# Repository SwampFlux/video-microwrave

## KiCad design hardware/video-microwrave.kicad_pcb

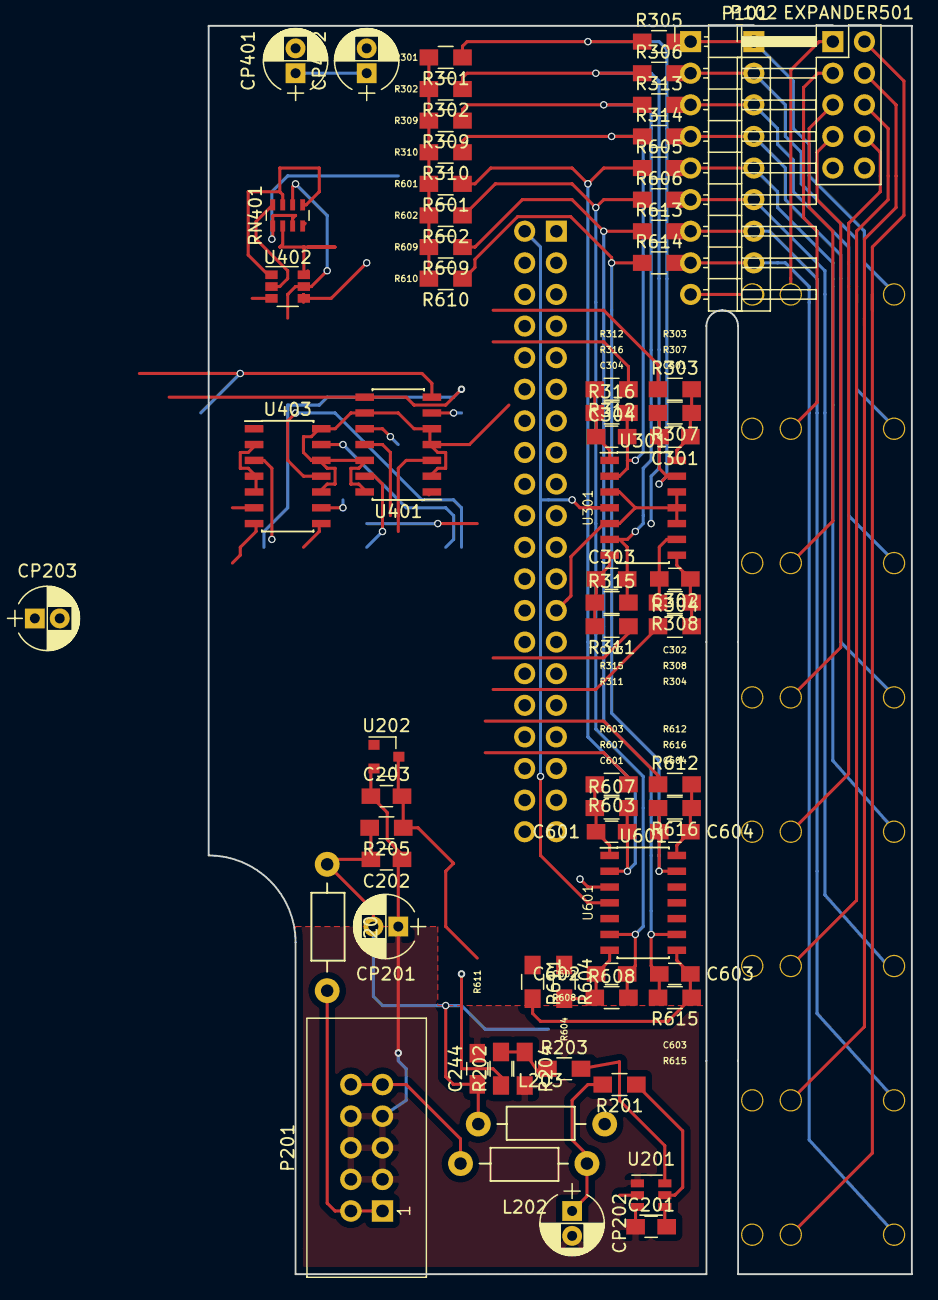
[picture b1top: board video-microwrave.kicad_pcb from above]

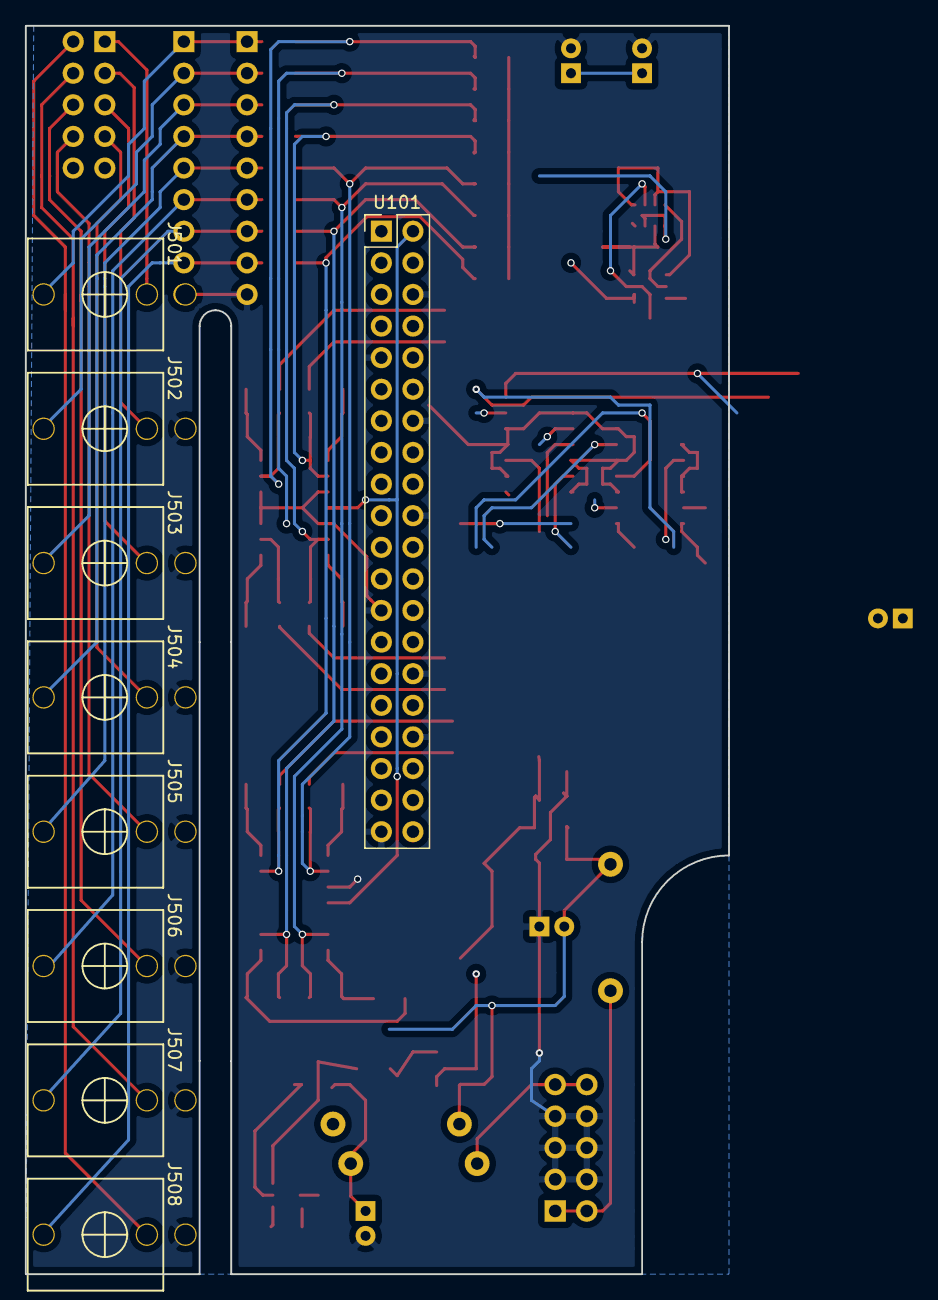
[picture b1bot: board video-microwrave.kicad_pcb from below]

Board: 2 copper layers, 56.5 x 100.3 mm, 78 parts (9 on the bottom side), 52 nets.

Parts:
C201, C244: 100nF; C_0805_HandSoldering
C202, C203: 1uF; C_0805_HandSoldering
C301, C302, C303, C304, C601, C602, C603, C604: 560pF; C_0805_HandSoldering
CP201, CP202, CP203: 22uF; CP_Radial_D5.0mm_P2.00mm
CP401: 100nF; CP_Radial_D5.0mm_P2.00mm
CP402: 10uF; CP_Radial_D5.0mm_P2.00mm
EXPANDER501: CONN_02X05; Pin_Header_Straight_2x05_Pitch2.54mm
J501, J502, J503, J504, J505, J506, J507, J508: PJ301M-12
L201, L202: 100nH; Choke_Horizontal_RM10mm
L203: 6u8H; Choke_Horizontal_RM10mm
P101: CONN_01X09; Pin_Header_Angled_1x09_Pitch2.54mm
P102: CONN_01X09; Pin_Header_Straight_1x09_Pitch2.54mm
P201: CONN_02X08; IDC_Header_Straight_10pins
R201: 100k; R_0805_HandSoldering
R202: 402k2; R_0805_HandSoldering
R203: 75k; R_0805_HandSoldering
R204: 7k68; R_0805_HandSoldering
R205: 2k; R_0805_HandSoldering
R301, R302, R309, R310, R601, R602, R609, R610: 499; R_0805_HandSoldering
R303, R304, R311, R312, R603, R604, R611, R612: 100R; R_0805_HandSoldering
R305, R306, R313, R314, R605, R606, R613, R614: 1k; R_0805_HandSoldering
R307, R308, R315, R316, R607, R608, R615, R616: 270; R_0805_HandSoldering
RN401: 10k; R_Array_Concave_4x0603
U101: Raspberry_Pi_Zero; Pin_Header_Straight_2x20_Pitch2.54mm
U201: LM1117-3.3; SOT-23-6
U202: NCP1117DT50G; SOT-23
U301, U601: MCP6004; SOIC-14_3.9x8.7mm_Pitch1.27mm
U401, U403: MCP3424; SOIC-14_3.9x8.7mm_Pitch1.27mm
U402: FDC6301N; SuperSOT-6

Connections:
+3V3: RN401.5, RN401.7, U101.1, U201.2, U201.4, U402.1, U402.3
+5V: C201.2, CP202.1, CP203.1, CP401.1, CP402.1, L202.1, L203.2, R202.1, RN401.1, RN401.3, U101.2, U101.4, U301.4, U401.6, U401.10, U403.6, U403.9, U601.4
/CV jacks/expansion1: EXPANDER501.1, J501.2
/CV jacks/expansion2: EXPANDER501.3, J502.2
/CV jacks/expansion3: EXPANDER501.5, J503.2
/CV jacks/expansion4: EXPANDER501.7, J504.2
/CV jacks/expansion5: EXPANDER501.8, J505.2
/CV jacks/expansion6: EXPANDER501.6, J506.2
/CV jacks/expansion7: EXPANDER501.4, J507.2
/CV jacks/expansion8: EXPANDER501.2, J508.2
/I2C_clock: RN401.6, U101.5, U402.5
/I2C_data: RN401.8, U101.3, U402.2
/adc/SCL_5V: RN401.2, U401.8, U402.6, U403.8
/adc/SDA_5V: RN401.4, U401.7, U402.4, U403.7
/buffered_1: R303.1, U401.1
/buffered_2: R304.1, U401.3
/buffered_3: R311.1, U401.11
/buffered_4: R312.1, U401.13
/buffered_5: R603.1, U403.1
/buffered_6: R604.1, U403.3
/buffered_7: R611.1, U403.13
/buffered_8: R612.1, U403.11
/buffers 1-4/-5V: C203.2, R205.1, R301.2, R302.2, R309.2, R310.2, R601.2, R602.2, R609.2, R610.2, U202.3
/cv1_raw: J501.3, P101.1, P102.1, R305.2
/cv2_raw: J502.3, P101.2, P102.2, R306.2
/cv3_raw: J503.3, P101.3, P102.3, R313.2
/cv4_raw: J504.3, P101.4, P102.4, R314.2
/cv5_raw: J505.3, P101.5, P102.5, R605.2
/cv6_raw: J506.3, P101.6, P102.6, R606.2
/cv7_raw: J507.3, P101.7, P102.7, R613.2
/cv8_raw: J508.3, P101.8, P102.8, R614.2
/power/-12: L201.2, P201.1, P201.2
Earth: C201.1, C202.1, C203.1, C244.2, CP201.1, CP202.2, CP203.2, CP401.2, CP402.2, EXPANDER501.9, J501.1, J502.1, J503.1, J504.1, J505.1, J506.1, J507.1, J508.1, P101.9, P102.9, P201.3, P201.4, P201.5, P201.6, P201.7, P201.8, R204.2, U101.6, U101.9, U101.14, U101.20, U101.25, U101.30, U101.34, U101.39, U201.1, U202.2, U301.3, U301.5, U301.10, U301.11, U301.12, U401.2, U401.4, U401.5, U401.9, U401.12, U401.14, U403.2, U403.4, U403.5, U403.10, U403.12, U403.14, U601.3, U601.5, U601.10, U601.11, U601.12
unnamed: C301.1, R303.2, R307.1, U301.14
unnamed: C301.2, R301.1, R305.1, R307.2, U301.13
unnamed: C302.1, R304.2, R308.1, U301.8
unnamed: C302.2, R302.1, R306.1, R308.2, U301.9
unnamed: C303.1, R311.2, R315.1, U301.7
unnamed: C303.2, R309.1, R313.1, R315.2, U301.6
unnamed: C304.1, R312.2, R316.1, U301.1
unnamed: C304.2, R310.1, R314.1, R316.2, U301.2
unnamed: C601.1, R603.2, R607.1, U601.1
unnamed: C601.2, R601.1, R605.1, R607.2, U601.2
unnamed: C602.1, R604.2, R608.1, U601.7
unnamed: C602.2, R602.1, R606.1, R608.2, U601.6
unnamed: C603.1, R611.2, R615.1, U601.8
unnamed: C603.2, R609.1, R613.1, R615.2, U601.9
unnamed: C604.1, R612.2, R616.1, U601.14
unnamed: C604.2, R610.1, R614.1, R616.2, U601.13
unnamed: L203.1, U201.3
unnamed: R202.2, R203.1, R204.1
VEE: C202.2, C244.1, CP201.2, L201.1, R205.2

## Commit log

2018-05-10 started kicad project
2018-05-10 connected SPI
2018-05-10 created eight jacks, pots, and connected separate ground for analog/digital lines. 5V power for everything. Wires ditched for global labels.
2018-05-10 started adding footprints
2018-05-30 copying a ton of stuff from other places.
2018-07-16 started 3d mockup
2018-07-17 added mocks for female header, micro sd, mini hdmi, and micro usb
2018-07-17 added old attempt to write julianna's textures as a fragment shader
2018-07-21 accurate measurements for pi zero, micro sd, panel, jacks, mini USB and HDMI
2018-07-21 Kobiconn jacks take up less space and have pins in a better position.
2018-07-22 Lots of my previous measurements were way off. Front panel is made of bezier curves now, and a ton of other things.
2018-07-24 more thought put into the support structure and wavy panel. still doesn't feel right though.
2018-07-24 moved jacks closer to the edge and mocked up knurled screws.
2018-07-25 Now pretty sure that I'll use vertical kobiconn jacks
2018-07-26 use freestyle to export front panel as svg. It ain't pretty.. but it's something. proper trace will need to be a real svg.
2018-11-07 buffered cv borrowed from O_C, adc circuit borrowed from ADC Pi. everything still wip
2018-11-08 power added to second adc
2018-11-08 four inputs mapped out with footprints
2018-11-08 jacks on a different sheet than the buffers. single PCB with jumpers and mouse bites
2018-11-09 most of the scematic is complete with the exception of the -5V offset
2018-11-13 updated footprint & first tracks laid
2018-11-13 finalized most footprints and nets.
2018-11-14 nearly there. 3.3v power supply is missing though
2018-11-15 looking pretty ugly, but very close
2018-11-15 still some unconnected pads, but might be good enough for a prototype. marked rev1
2018-11-15 before I fix alignment issues with the rest of the module
2018-11-16 experimental svg exports & slight 3d model adjustments
2018-11-18 open frameworks for software rewrite started
2018-11-18 renamed ofx directory
2018-11-29 moving footprints to fit real world dimensions
2018-11-29 made space for an expansion connector. net needs updating for 8 100k resistors coming from raw signals
2018-11-30 reworked input board
2018-12-02 shoved op amp into 1cm space
2018-12-02 removal of +12 to +5 stepdown since i've got no CV outputs.
2018-12-02 planned 5V and 3.3V lines
2018-12-04 reworking front panel to double as side support structure
2018-12-04 rearranged layers, designated bend objects, realigned screws, tapered screws
2018-12-04 rotated first op amp & shofted 40-pin connector to match 3d model
2018-12-22 removing ofx. starting python wrapper for glslViewer
2018-12-24 ADCPi integrated with glslViewer python wrapper
2018-12-24 first channel given multiple types for cv to unform conversion. needs to be made functional
2019-09-12 Created funding link
    i could use dollars please
2020-07-19 some of the tarot cards made. new python wrapper started
2020-07-22 new python wrapper. doesn't work yet but a nice start
2020-07-22 python wrapper for ADCpi works okay but is slow
2020-07-23 renamed a bunch of software files. made ADCPi a pip package
2020-07-23 migrated every old software to resources. pulled dependencies as submodules
2020-07-23 wow i suck at cpp
2020-07-23 fixing submodule paths
2020-07-23 moved submodule files
2020-07-23 goodbye swap file
2020-07-26 sorta making progress with the Makefile
2020-07-27 undefined reference to oscpack
2020-07-27 closest I've gotten. main compiles, but ip/NetworkingUtils.h file not found
2020-07-27 might work
2020-07-28 RIppy helped me compile! Yay!
2020-07-28 out of memory error fixed.
2020-07-30 turned on all 8 channels but it's very slow
2020-08-08 Updates for KiCAD5. Reverted schematic to MCP3008
2020-08-12 updating old shaders. revisited original mcp3008 code.
2021-03-21 upgraded kicad
